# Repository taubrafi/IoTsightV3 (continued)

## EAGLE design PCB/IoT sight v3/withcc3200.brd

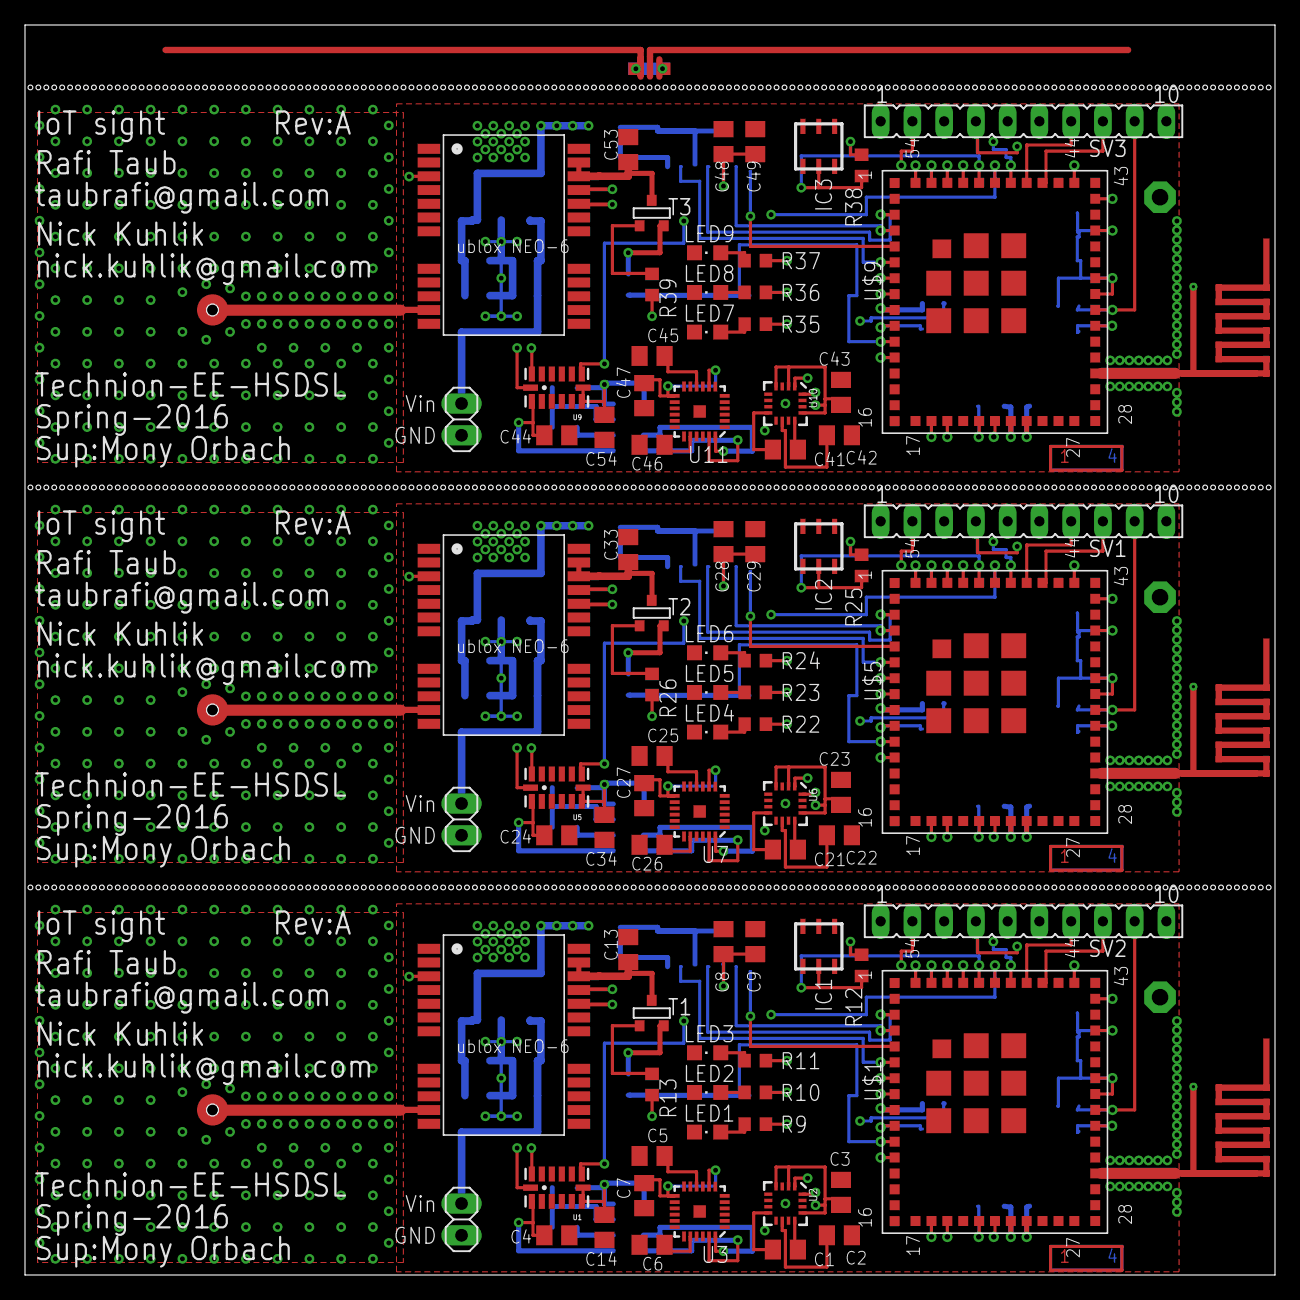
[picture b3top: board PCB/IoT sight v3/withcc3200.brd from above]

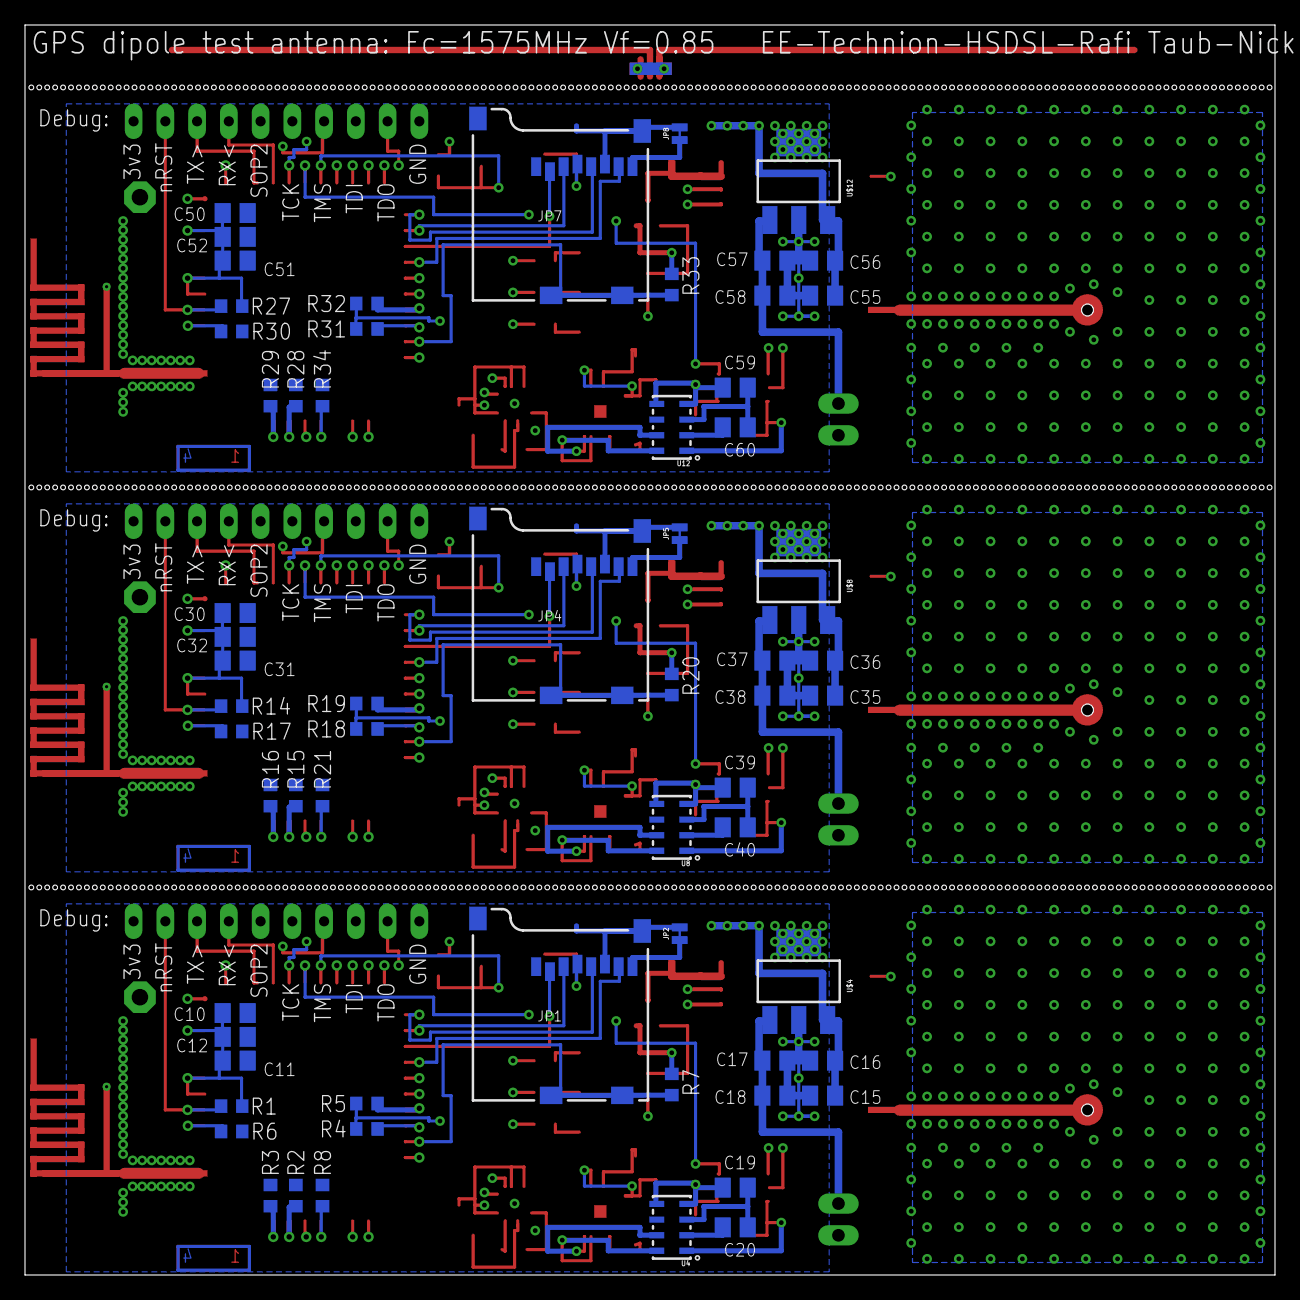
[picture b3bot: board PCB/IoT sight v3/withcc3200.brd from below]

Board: 4 copper layers, 100.0 x 100.0 mm, 153 parts (63 on the bottom side), 123 nets.

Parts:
ANT1, ANT2, ANT3: ADA18182; PAD-01
C1, C21, C41: 0.22uF; C0805K
C2, C8, C10, C15, C17, C22, C28, C30, C35, C37, C42, C48, C50, C55, C57: 4.7uf; C0805K
C3, C4, C5, C7, C9, C11, C13, C14, C16, C18, C23, C24, C25, C27, C29, C31, C33, C34, C36, C38, C43, C44, C45, C47, C49, C51, C53, C54, C56, C58: 0.1uF; C0805K
C6, C26, C46: 2.2nf; C0805K
C12, C32, C52: 0.01uF; C0805K
C19, C20, C39, C40, C59, C60: 1uF; C0805K
IC1, IC2, IC3: DS2401P; TSOC6
JP1, JP4, JP7: 2908-05WB-MG; MICRO-SD-SOCKET-SDIO
JP2, JP5, JP8: JUMPER-PAD-2-NC_BY_TRACENO_SILK; PAD-JUMPER-2-NC_BY_TRACE_NO_SILK
JP3, JP6, JP9: 1X02
LED1, LED2, LED3, LED4, LED5, LED6, LED7, LED8, LED9: CHIPLED_0805
R1, R7, R14, R20, R27, R33: 10k; R0603
R2, R4, R5, R12, R13, R15, R18, R19, R25, R26, R28, R31, R32, R38, R39: 2.7k; R0603
R3, R6, R8, R16, R17, R21, R29, R30, R34: 100k; R0603
R9, R10, R11, R22, R23, R24, R35, R36, R37: 470R; R0603
SV1, SV2, SV3: FE10
T1, T2, T3: BS250; SOT-23
U1, U5, U9: ADXL345; LGA14
U2, U6, U10: HMC5883LSMD; 16LPCC
U3, U7, U11: ITG-3200ORIG; QFN-24
U4, U8, U12: MPL115A2; LGA8
U$1, U$5, U$9: CC3200MOD
U$2, U$6, U$10: UBLOX_NEO-7; UBLOX_NEO-6P
U$3, U$7, U$11: FOUR_LAYER_WARNING
U$4, U$8, U$12: MIC2920A-3.3WS-TR; SOT223

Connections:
ACC_INT1: U1.8, U$1.P49
ACC_INT3: U5.8, U$5.P49
ACC_INT5: U9.8, U$9.P49
GND: ANT1.1, C2.2, C3.2, C4.2, C5.2, C6.2, C7.2, C8.2, C9.2, C10.2, C11.2, C12.2, C13.2, C14.2, C15.2, C16.2, C17.2, C18.2, C19.2, C20.2, IC1.1, JP1.GND, JP1.GND1, JP1.GND3, JP2.2, JP3.1, LED1.C, LED2.C, LED3.C, R2.1, R3.1, R6.1, R8.1, SV2.1, U1.2, U1.4, U1.5, U1.12, U2.9, U2.11, U3.1, U3.9, U3.11, U3.18, U4.3, U$1.P1, U$1.P2, U$1.P16, U$1.P27, U$1.P28, U$1.P30, U$1.P32, U$1.P38, U$1.P43, U$1.P55, U$1.P56, U$1.P57, U$1.P58, U$1.P59, U$1.P60, U$1.P61, U$1.P62, U$1.P63, U$2.7_VDDUSB, U$2.10_GND, U$2.12_GND, U$2.13_GND, U$2.24_GND, U$4.2
GND1: ANT2.1, C22.2, C23.2, C24.2, C25.2, C26.2, C27.2, C28.2, C29.2, C30.2, C31.2, C32.2, C33.2, C34.2, C35.2, C36.2, C37.2, C38.2, C39.2, C40.2, IC2.1, JP4.GND, JP4.GND1, JP4.GND3, JP5.2, JP6.1, LED4.C, LED5.C, LED6.C, R15.1, R16.1, R17.1, R21.1, SV1.1, U5.2, U5.4, U5.5, U5.12, U6.9, U6.11, U7.1, U7.9, U7.11, U7.18, U8.3, U$5.P1, U$5.P2, U$5.P16, U$5.P27, U$5.P28, U$5.P30, U$5.P32, U$5.P38, U$5.P43, U$5.P55, U$5.P56, U$5.P57, U$5.P58, U$5.P59, U$5.P60, U$5.P61, U$5.P62, U$5.P63, U$6.7_VDDUSB, U$6.10_GND, U$6.12_GND, U$6.13_GND, U$6.24_GND, U$8.2
GND2: ANT3.1, C42.2, C43.2, C44.2, C45.2, C46.2, C47.2, C48.2, C49.2, C50.2, C51.2, C52.2, C53.2, C54.2, C55.2, C56.2, C57.2, C58.2, C59.2, C60.2, IC3.1, JP7.GND, JP7.GND1, JP7.GND3, JP8.2, JP9.1, LED7.C, LED8.C, LED9.C, R28.1, R29.1, R30.1, R34.1, SV3.1, U9.2, U9.4, U9.5, U9.12, U10.9, U10.11, U11.1, U11.9, U11.11, U11.18, U12.3, U$9.P1, U$9.P2, U$9.P16, U$9.P27, U$9.P28, U$9.P30, U$9.P32, U$9.P38, U$9.P43, U$9.P55, U$9.P56, U$9.P57, U$9.P58, U$9.P59, U$9.P60, U$9.P61, U$9.P62, U$9.P63, U$10.7_VDDUSB, U$10.10_GND, U$10.12_GND, U$10.13_GND, U$10.24_GND, U$12.2
GPS_ON: R13.2, U$1.P54
GPS_ON1: R26.2, U$5.P54
GPS_ON2: R39.2, U$9.P54
ID: IC1.2, R12.1, U$1.P50
ID1: IC2.2, R25.1, U$5.P50
ID2: IC3.2, R38.1, U$9.P50
JTAG_TCK: R8.2, SV2.5, U$1.P21
JTAG_TCK1: R21.2, SV1.5, U$5.P21
JTAG_TCK2: R34.2, SV3.5, U$9.P21
JTAG_TDI: SV2.3, U$1.P12
JTAG_TDI1: SV1.3, U$5.P12
JTAG_TDI2: SV3.3, U$9.P12
JTAG_TDO: SV2.2, U$1.P18
JTAG_TDO1: SV1.2, U$5.P18
JTAG_TDO2: SV3.2, U$9.P18
JTAG_TMS: SV2.4, U$1.P22
JTAG_TMS1: SV1.4, U$5.P22
JTAG_TMS2: SV3.4, U$9.P22
LED1: R9.2, U$1.P51
LED2: R10.2, U$1.P52
LED3: R11.2, U$1.P53
LED4: R22.2, U$5.P51
LED5: R23.2, U$5.P52
LED6: R24.2, U$5.P53
LED7: R35.2, U$9.P51
LED8: R36.2, U$9.P52
LED9: R37.2, U$9.P53
unnamed: JP1.DAT1, JP2.1
unnamed: C1.2, U2.12
unnamed: C1.1, U2.8
unnamed: C2.1, U2.10
unnamed: LED1.A, R9.1
unnamed: LED2.A, R10.1
unnamed: C5.1, U3.10
unnamed: LED3.A, R11.1
unnamed: C6.1, U3.20
unnamed: C17.1, C18.1, JP3.2, U$4.1
unnamed: C13.1, T1.1, U$2.22_V_BCKP, U$2.23_VCC
unnamed: R13.1, T1.3
unnamed: C20.1, U4.2
unnamed: C21.2, U6.12
unnamed: C21.1, U6.8
unnamed: C22.1, U6.10
unnamed: C25.1, U7.10
unnamed: C26.1, U7.20
unnamed: JP4.DAT1, JP5.1
unnamed: LED4.A, R22.1
unnamed: LED5.A, R23.1
unnamed: LED6.A, R24.1
unnamed: C37.1, C38.1, JP6.2, U$8.1
unnamed: C33.1, T2.1, U$6.22_V_BCKP, U$6.23_VCC
unnamed: R26.1, T2.3
unnamed: C40.1, U8.2
unnamed: C41.2, U10.12
unnamed: C41.1, U10.8
unnamed: C42.1, U10.10
unnamed: C45.1, U11.10
unnamed: C46.1, U11.20
unnamed: JP7.DAT1, JP8.1
unnamed: LED7.A, R35.1
unnamed: LED8.A, R36.1
unnamed: LED9.A, R37.1
unnamed: C57.1, C58.1, JP9.2, U$12.1
unnamed: C53.1, T3.1, U$10.22_V_BCKP, U$10.23_VCC
unnamed: R39.1, T3.3
unnamed: C60.1, U12.2
NRST: R1.1, SV2.9, U$1.P35
NRST1: R14.1, SV1.9, U$5.P35
NRST2: R27.1, SV3.9, U$9.P35
RX1: U$1.P8, U$2.20_TXD1
RX2: U$5.P8, U$6.20_TXD1
RX3: U$9.P8, U$10.20_TXD1
RXD: SV2.7, U$1.P47
RXD1: SV1.7, U$5.P47
RXD2: SV3.7, U$9.P47
SCL: R5.1, U1.14, U2.1, U3.23, U4.8, U$1.P9
SCL1: R19.1, U5.14, U6.1, U7.23, U8.8, U$5.P9
SCL2: R32.1, U9.14, U10.1, U11.23, U12.8, U$9.P9
SDA: R4.1, U1.13, U2.16, U3.24, U4.7, U$1.P10
SDA1: R18.1, U5.13, U6.16, U7.24, U8.7, U$5.P10
SDA2: R31.1, U9.13, U10.16, U11.24, U12.7, U$9.P10
SD_CARD_DET: JP1.CD1, JP1.CD2, R7.1, U$1.P11
SD_CARD_DET1: JP4.CD1, JP4.CD2, R20.1, U$5.P11
SD_CARD_DET2: JP7.CD1, JP7.CD2, R33.1, U$9.P11
SD_CLK: JP1.CLK, U$1.P3
SD_CLK1: JP4.CLK, U$5.P3
SD_CLK2: JP7.CLK, U$9.P3
SD_CMD: JP1.CMD, U$1.P4
SD_CMD1: JP4.CMD, U$5.P4
SD_CMD2: JP7.CMD, U$9.P4
SD_CS: JP1.CD/DAT3, U$1.P5
SD_CS1: JP4.CD/DAT3, U$5.P5
SD_CS2: JP7.CD/DAT3, U$9.P5
SD_DATA0: JP1.DAT0, U$1.P6
SD_DATA1: JP4.DAT0, U$5.P6
SD_DATA2: JP7.DAT0, U$9.P6
SOP0: R6.2, U$1.P34
SOP1: R3.2, U$1.P24
SOP2: R2.2, SV2.6, U$1.P23
SOP3: R17.2, U$5.P34
SOP4: R16.2, U$5.P24
SOP5: R15.2, SV1.6, U$5.P23
SOP6: R30.2, U$9.P34
SOP7: R29.2, U$9.P24
SOP8: R28.2, SV3.6, U$9.P23
TIMEPULSE: U$1.P48, U$2.3_TIMEPULSE
TIMEPULSE1: U$5.P48, U$6.3_TIMEPULSE
TIMEPULSE2: U$9.P48, U$10.3_TIMEPULSE
TX1: U$1.P7, U$2.21_RXD1
TX2: U$5.P7, U$6.21_RXD1
TX3: U$9.P7, U$10.21_RXD1
TXD: SV2.8, U$1.P46
TXD1: SV1.8, U$5.P46
TXD2: SV3.8, U$9.P46
VDD: C3.1, C4.1, C7.1, C8.1, C9.1, C10.1, C11.1, C12.1, C14.1, C15.1, C16.1, C19.1, JP1.VCC, R1.2, R4.2, R5.2, R7.2, R12.2, SV2.10, T1.2, U1.1, U1.6, U1.7, U2.2, U2.4, U2.13, U3.8, U3.13, U4.1, U4.4, U4.5, U$1.P36, U$1.P37, U$1.P40, U$4.3
VDD1: C23.1, C24.1, C27.1, C28.1, C29.1, C30.1, C31.1, C32.1, C34.1, C35.1, C36.1, C39.1, JP4.VCC, R14.2, R18.2, R19.2, R20.2, R25.2, SV1.10, T2.2, U5.1, U5.6, U5.7, U6.2, U6.4, U6.13, U7.8, U7.13, U8.1, U8.4, U8.5, U$5.P36, U$5.P37, U$5.P40, U$8.3
VDD2: C43.1, C44.1, C47.1, C48.1, C49.1, C50.1, C51.1, C52.1, C54.1, C55.1, C56.1, C59.1, JP7.VCC, R27.2, R31.2, R32.2, R33.2, R38.2, SV3.10, T3.2, U9.1, U9.6, U9.7, U10.2, U10.4, U10.13, U11.8, U11.13, U12.1, U12.4, U12.5, U$9.P36, U$9.P37, U$9.P40, U$12.3

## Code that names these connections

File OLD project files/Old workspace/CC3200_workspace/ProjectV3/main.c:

//*****************************************************************************
// Copyright (C) 2014 Texas Instruments Incorporated
//
// All rights reserved. Property of Texas Instruments Incorporated.
// Restricted rights to use, duplicate or disclose this code are
// granted through contract.
// The program may not be used without the written permission of
// Texas Instruments Incorporated or against the terms and conditions
// stipulated in the agreement under which this program has been supplied,
// and under no circumstances can it be used with non-TI connectivity device.
//
//*****************************************************************************


//*****************************************************************************
//
// Application Name     - HTTP Client Demo
// Application Overview - This sample application demonstrates how to use
//                          HTTP Client (In Minimum mode) API for HTTP based
//                          application development.
//                          This application explain user to how to:
//                          1. Connect to an access point
//                          2. Connect to a HTTP Server with and without proxy
//                          3. Do POST, GET, PUT and DELETE
//                          4. Parse JSON data using Jasmine JSON Parser
// Note: To use HTTP Client in minimum mode, user need to compile library (webclient)
// 			with HTTPCli_LIBTYPE_MIN option.
//
// 			HTTP Client (minimal) library supports synchronous mode, redirection
// 			handling, chunked transfer encoding support, proxy support and TLS
// 			support (for SimpleLink Only. TLS on other platforms are disabled)
//
// 			HTTP Client (Full) library supports all the features of the minimal
// 			library + asynchronous mode and content handling support +
// 			TLS support (all platforms). To use HTTP Client in full mode user need
//			to compile library (webclient) with HTTPCli_LIBTYPE_MIN option. For full
//			mode RTOS is needed.
//
// Application Details  -
// http://processors.wiki.ti.com/index.php/
// or
// docs\examples\
//
//*****************************************************************************


#include "includes.h"



//*****************************************************************************
//                 GLOBAL VARIABLES -- Start
//*****************************************************************************

#if defined(ccs) || defined(gcc)
extern void (* const g_pfnVectors[])(void);
#endif
#if defined(ewarm)
extern uVectorEntry __vector_table;
#endif


//*****************************************************************************
//
//! Application startup display on UART
//!
//! \param  none
//!
//! \return none
//!
//*****************************************************************************
static void
DisplayBanner(char * AppName)
{
	UART_PRINT("\n\n\n\r");
	UART_PRINT("\t\t *************************************************\n\r");
	UART_PRINT("\t\t      CC3200 %s Application       \n\r", AppName);
	UART_PRINT("\t\t *************************************************\n\r");
	UART_PRINT("\n\n\n\r");
}


//*****************************************************************************
//
//! Board Initialization & Configuration
//!
//! \param  None
//!
//! \return None
//
//*****************************************************************************
static void
BoardInit(void)
{

	IntVTableBaseSet((unsigned long)&g_pfnVectors[0]);

	IntMasterEnable();
	IntEnable(FAULT_SYSTICK);

	PRCMCC3200MCUInit();
}

char printing;

void UART1_Handler(void)
{
	unsigned long UART_STATUS;
	//	char stringinging[] = "$GPRMC,165431.00,A,4029.88110,N,07424.85655,W,0.492,,030816,,,A*64";

	UART_STATUS = UARTIntStatus(UARTA1_BASE, true);
	UARTIntClear(UARTA1_BASE, UART_INT_RX);
	UARTIntDisable(UARTA1_BASE, UART_INT_RX);



	while((UART_STATUS & UART_INT_RX) && UARTCharsAvail(UARTA1_BASE))
	{
		printing = (char) UARTCharGetNonBlocking(UARTA1_BASE);
		//	printing = stringinging[kkk++];
		//	if(kkk>strlen(stringinging)) kkk=0;
		ParseGPS(printing);
		//if(gpsFix==0)	UART_PRINT(&printing);
	}

	UARTIntEnable(UARTA1_BASE, UART_INT_RX);
}




int main()
{
	long lRetVal = -1;
	HTTPCli_Struct httpClient;
	char pBuffer[100];



	BoardInit();
	PinMuxConfig();

	InitTerm();
	//
	// Clearing the Terminal.
	//
	ClearTerm();
	//GPIO_IF_LedConfigure(LED1|LED2|LED3);
	DisplayBanner(APP_NAME);

	init_HMC5883(MAG_ADDR, true);
	init_ADXL345(ACC_ADDR);
	init_MPL115A2();
	init_ds2401();
	init_SD_card();

	GPS_on();

	SD_write_file("hello.txt", "my name is", strlen("my name is"), SD_CREATE_AND_DELETE);

	char strbuffer[100];
	char databuf[100];

	float Xmag=-1, Ymag=-1, Zmag=-1;
	float Xacc=-1, Yacc=-1, Zacc=-1;
	double roll=-1, pitch=-1, yaw=-1;
	float accMag=-1;

	float pressure;

	//int kkkk;
	/*InitializeAppVariables();

	UART_PRINT("\n\r\n\rStops here on failure caused by debug!\n\r\n\r");
	lRetVal = ConnectToAP();

	if(lRetVal < 0)
	{
		LOOP_FOREVER();
	}

	lRetVal = ConnectToHTTPServer(&httpClient);
	if(lRetVal < 0)
	{
		LOOP_FOREVER();
	}
	UART_PRINT("Connected to server!\n\r\n\r");
	 */

	while(1)
	{
		//if(gpsFix==1)
		UART_PRINT("\33[H\33[2J");

		if(HMC5883_read_magdata(MAG_ADDR, &Xmag, &Ymag, &Zmag)<0) UART_PRINT("!!! mag I2c Error\n\r");
		if(ADXL345_read_accdata(ACC_ADDR, &Xacc, &Yacc, &Zacc)<0) UART_PRINT("!!! acc I2c Error\n\r");
		accMag = sqrt(Xacc*Xacc + Yacc*Yacc + Zacc*Zacc);

		IMU_calculate(-Xacc/accMag, -Yacc/accMag, Zacc/accMag, -Xmag, -Ymag, Zmag, &roll, &pitch, &yaw);
		sprintf(databuf,"MAG=(%5f, %5f, %5f) ACC=(%5f, %5f, %5f)\n\r(roll, pitch, yaw) = (%5f, %5f, %5f)\n\r", Xmag, Ymag, Zmag, Xacc/accMag, Yacc/accMag, Zacc/accMag, roll, pitch, yaw);
		UART_PRINT(databuf);

		sprintf(databuf,"Time:%d.%05d\n\rDate:%d\n\rLat:%ld Long:%ld\n\rFix:%s\n\r",
				gpsTime, gpsMsecs, gpsDate, gpsLat, gpsLong, (gpsFix>0)?"Yes":"No");
		UART_PRINT(databuf);

		sprintf(databuf,"X: %f    %f\n\rY:%f    %f\n\rZ:%f    %f\n\r",
				Xmin, Xmax, Ymin, Ymax, Zmin, Zmax);
		UART_PRINT(databuf);

		sprintf(databuf,"ID=%lld\n\r", ds2401_get_id_long());
		UART_PRINT(databuf);

		if(MPL115A2_get_pressure(&pressure)<0) UART_PRINT("!!! bar I2c Error\n\r");
		sprintf(pBuffer,"pressure=%fkPa\n\r", pressure);
		UART_PRINT(pBuffer);

		/*
		sprintf(strbuffer,"/shots/get/12345/%d/%d/0/%d", (int)roll, (int)pitch, (int)yaw);
		lRetVal = HTTPGetMethod(&httpClient, strbuffer);
		if(lRetVal < 0)
		{
			UART_PRINT("HTTP Post Get failed.\n\r");
		}
		UART_PRINT("HTTP Get sent to server!\n\r\n\r");
		 */

		UtilsDelay(2666667);
	}

	HTTPCli_disconnect(&httpClient);
	sl_WlanDisconnect();
	UART_PRINT("Connection closed.\n\r");
	//LOOP_FOREVER();
	return 0;
}


void shot_routine(void)
{

}

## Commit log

2016-08-08 :space_invader: Added .gitattributes & .gitignore files
2016-08-08 Initial
2016-08-08 Second
2016-12-10 Final
    Final version
2016-12-10 FinalV3
    Final project with updated documentation
